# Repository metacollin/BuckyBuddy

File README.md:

# Cyclone V Bucky Buddy
<sub><sup><br /><span xmlns:dct="http://purl.org/dc/terms/" property="dct:title">Cyclone V Bucky Buddy</span> by <a xmlns:cc="http://creativecommons.org/ns#" href="https://github.com/metacollin/buckybuddy" property="cc:attributionName" rel="cc:attributionURL">metacollin</a> is licensed under a <a rel="license" href="http://creativecommons.org/licenses/by-nc-sa/4.0/">Creative Commons Attribution-NonCommercial-ShareAlike 4.0 International License</a>.</sup></sub>

BOM and component placement files are in the BOMAndPlace folder, shematics are in the Schematics folder. Board is available on [OSHpark](https://oshpark.com/shared_projects/RDkRPXU1).

The repository directory is a standard KiCad project and all CAD files are in KiCad format.

Schematic:

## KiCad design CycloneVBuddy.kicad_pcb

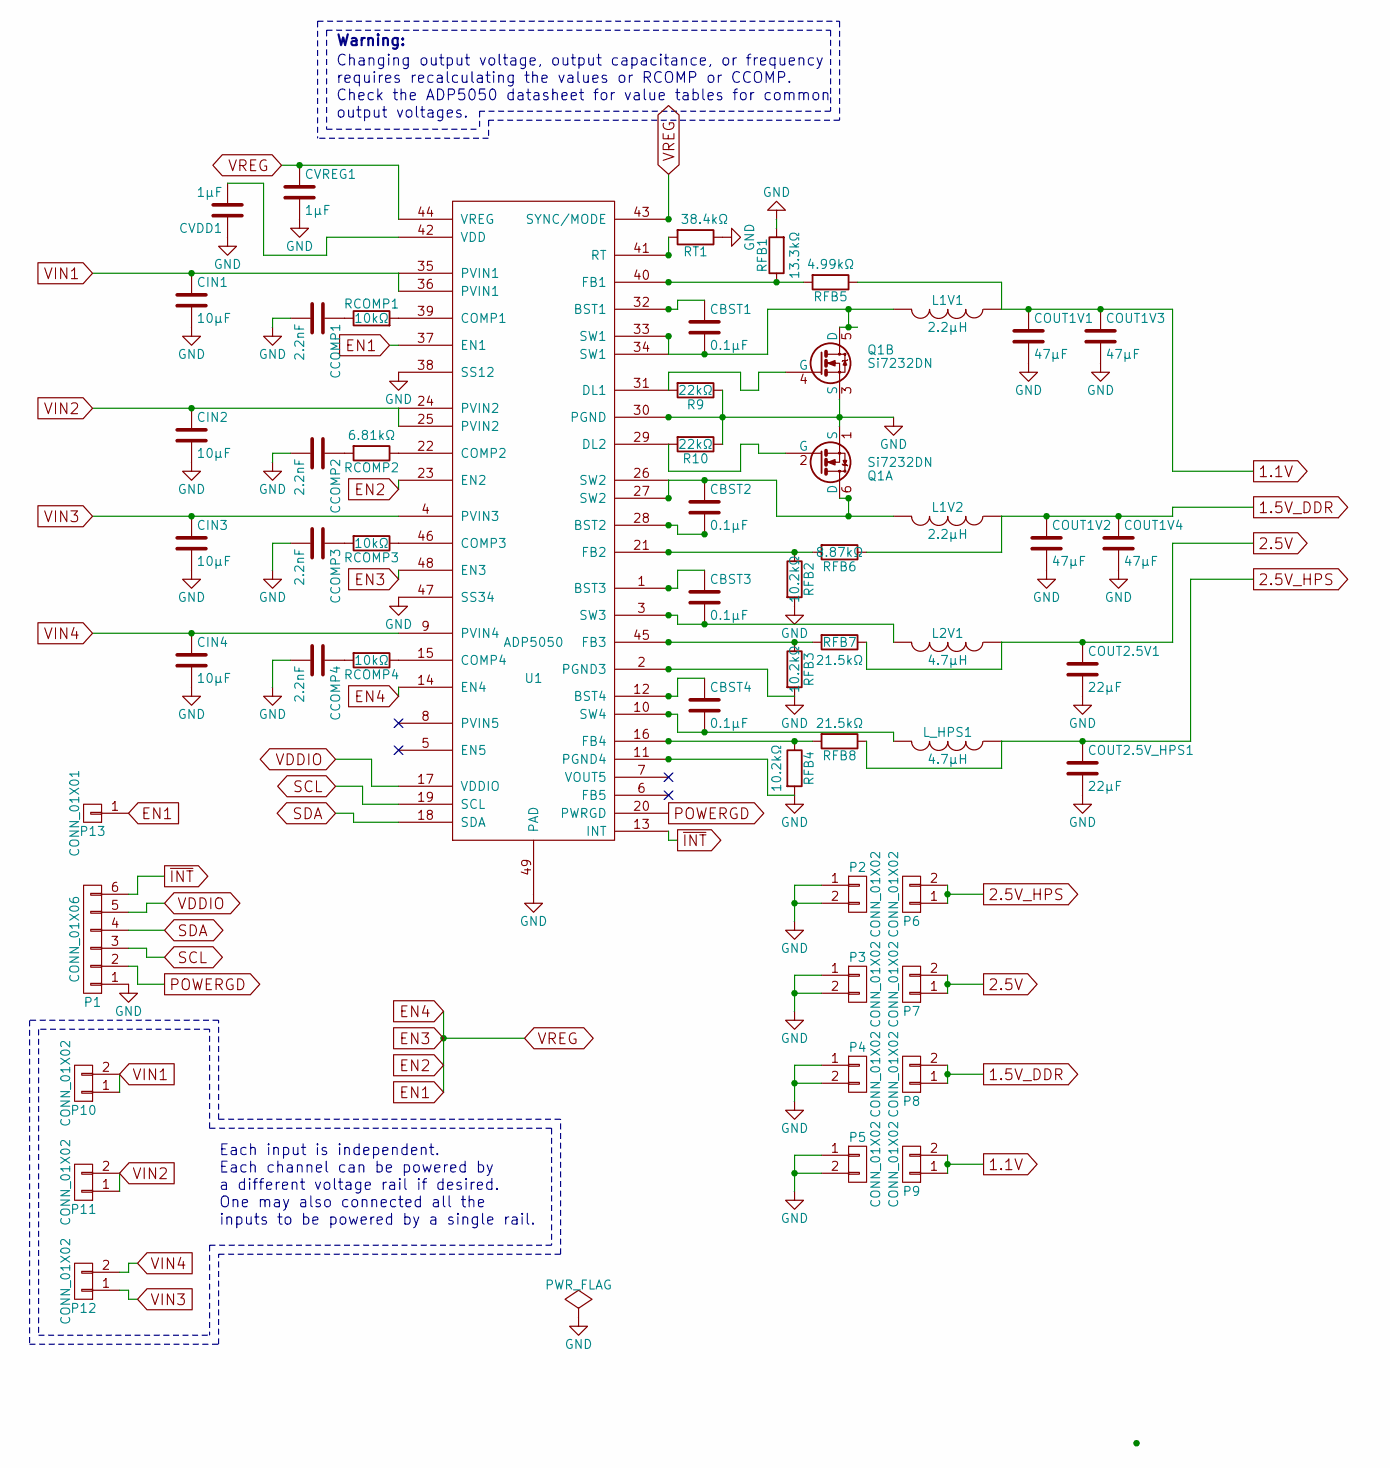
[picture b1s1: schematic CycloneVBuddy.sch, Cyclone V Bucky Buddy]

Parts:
CBST1, CBST2, CBST3, CBST4: 0.1µF; C_0402
CCOMP1, CCOMP2, CCOMP3, CCOMP4: 2.2nF; C_0402
CIN1, CIN2, CIN3, CIN4: 10µF; C_0805
COUT1V1, COUT1V2, COUT1V3, COUT1V4: 47µF; C_0805
COUT2.5V1, COUT2.5V_HPS1: 22µF; C_0603
CVDD1: 1µF; C_0402
CVREG1: 1µF; C_0402
L1V1, L1V2: 2.2µH; TYD6045
L2V1: 4.7µH; TYD6045
L_HPS1: 4.7µH; TYD6045
P1: CONN_01X06; Castillated_6
P2, P3, P4, P5, P6, P7, P8, P9, P10, P11, P12: CONN_01X02; Castillated_2
P13: CONN_01X01; Castillated_1
Q1: Si7232DN; PowerPak1212
R9, R10: 22kΩ; R_0402
RCOMP1, RCOMP3, RCOMP4: 10kΩ; R_0402
RCOMP2: 6.81kΩ; R_0402
RFB1: 13.3kΩ; R_0402
RFB2, RFB3, RFB4: 10.2kΩ; R_0402
RFB5: 4.99kΩ; R_0402
RFB6: 8.87kΩ; R_0402
RFB7, RFB8: 21.5kΩ; R_0402
RT1: 38.4kΩ; R_0402
U1: ADP5050; QFN-48-TE

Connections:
1.1V: COUT1V1.1, COUT1V3.1, L1V1.1, P9.1, P9.2, RFB5.1
1.5V_DDR: COUT1V2.1, COUT1V4.1, L1V2.1, P8.1, P8.2, RFB6.1
2.5V: COUT2.5V1.1, L2V1.1, P7.1, P7.2, RFB7.1
2.5V_HPS: COUT2.5V_HPS1.1, L_HPS1.1, P6.1, P6.2, RFB8.1
EN1: CVREG1.1, P13.1, U1.14 (EN4), U1.23 (EN2), U1.37 (EN1), U1.43 (SYNC/MODE), U1.44 (VREG), U1.48 (EN3)
GND: CCOMP1.2, CCOMP2.2, CCOMP3.2, CCOMP4.2, CIN1.2, CIN2.2, CIN3.2, CIN4.2, COUT1V1.2, COUT1V2.2, COUT1V3.2, COUT1V4.2, COUT2.5V1.2, COUT2.5V_HPS1.2, CVDD1.1, CVREG1.2, P1.1, P2.1, P2.2, P3.1, P3.2, P4.1, P4.2, P5.1, P5.2, Q1.1 (S), Q1.3 (S), R9.1, R10.1, RFB1.2, RFB2.2, RFB3.2, RFB4.2, RT1.1, U1.2 (PGND3), U1.11 (PGND4), U1.30 (PGND), U1.38 (SS12), U1.47 (SS34), U1.49 (PAD)
unnamed: CBST1.1, U1.32 (BST1)
unnamed: CBST1.2, L1V1.2, Q1.5 (D), U1.33 (SW1), U1.34 (SW1)
unnamed: CBST2.1, L1V2.2, Q1.6 (D), U1.26 (SW2), U1.27 (SW2)
unnamed: CBST2.2, U1.28 (BST2)
unnamed: CBST3.1, U1.1 (BST3)
unnamed: CBST3.2, L2V1.2, U1.3 (SW3)
unnamed: CBST4.1, U1.12 (BST4)
unnamed: CBST4.2, L_HPS1.2, U1.10 (SW4)
unnamed: CCOMP1.1, RCOMP1.1
unnamed: CCOMP2.1, RCOMP2.2
unnamed: CCOMP3.1, RCOMP3.2
unnamed: CCOMP4.1, RCOMP4.2
unnamed: CVDD1.2, U1.42 (VDD)
unnamed: Q1.2 (G), R10.2, U1.29 (DL2)
unnamed: Q1.4 (G), R9.2, U1.31 (DL1)
unnamed: RCOMP1.2, U1.39 (COMP1)
unnamed: RCOMP2.1, U1.22 (COMP2)
unnamed: RCOMP3.1, U1.46 (COMP3)
unnamed: RCOMP4.1, U1.15 (COMP4)
unnamed: RFB1.1, RFB5.2, U1.40 (FB1)
unnamed: RFB2.1, RFB6.2, U1.21 (FB2)
unnamed: RFB3.1, RFB7.2, U1.45 (FB3)
unnamed: RFB4.1, RFB8.2, U1.16 (FB4)
unnamed: RT1.2, U1.41 (RT)
POWERGD: P1.2, U1.20 (PWRGD)
SCL: P1.3, U1.19 (SCL)
SDA: P1.4, U1.18 (SDA)
VDDIO: P1.5, U1.17 (VDDIO)
VIN1: CIN1.1, P10.1, P10.2, U1.35 (PVIN1), U1.36 (PVIN1)
VIN2: CIN2.1, P11.1, P11.2, U1.24 (PVIN2), U1.25 (PVIN2)
VIN3: CIN3.1, P12.1, U1.4 (PVIN3)
VIN4: CIN4.1, P12.2, U1.9 (PVIN4)
~INT: P1.6, U1.13 (INT)

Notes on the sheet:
Each input is independent. Each channel can be powered by a different voltage rail if desired. One may also connected all the inputs to be powered by a single rail.
Warning:
Changing output voltage, output capacitance, or frequency requires recalculating the values or RCOMP or CCOMP. Check the ADP5050 datasheet for value tables for common output voltages.

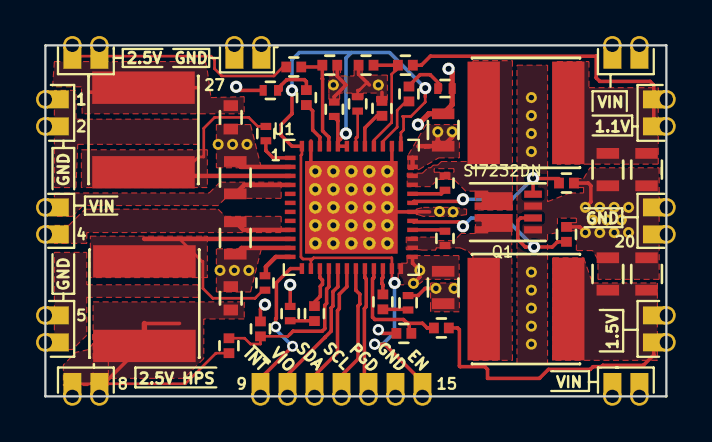
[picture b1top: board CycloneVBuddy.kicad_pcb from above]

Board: 2 copper layers, 34.5 x 19.5 mm, 54 parts (1 on the bottom side), 39 nets.

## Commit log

2015-09-17 Initial commit.
2015-09-18 Added Gerbers.
2015-10-27 Cleanup.
